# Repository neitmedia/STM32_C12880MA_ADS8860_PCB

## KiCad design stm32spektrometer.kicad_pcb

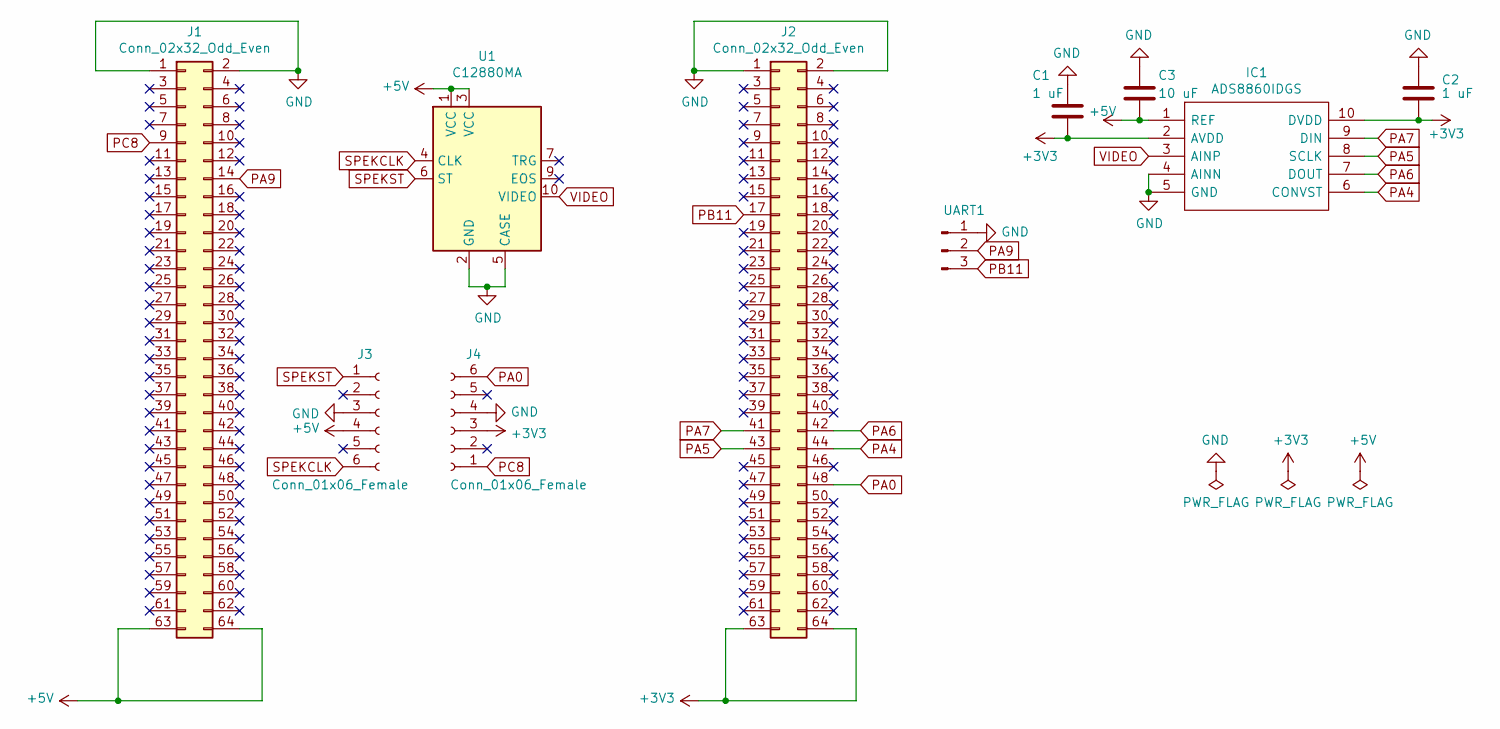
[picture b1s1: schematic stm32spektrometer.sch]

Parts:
C1, C2: 1 uF; C_0805_2012Metric
C3: 10 uF; C_0805_2012Metric
IC1: ADS8860IDGS; SOP50P490X110-10N; Mouser Part Number 595-ADS8860IDGS
J1, J2: Conn_02x32_Odd_Even; PinSocket_2x32_P2.54mm_Vertical
J3, J4: Conn_01x06_Female; PinSocket_1x06_P2.54mm_Vertical
U1: C12880MA; Hamamatsu_C12880
UART1: PinHeader_1x03_P2.54mm_Vertical

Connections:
+3V3: C1.2, C2.2, IC1.2 (AVDD), IC1.10 (DVDD), J2.63, J2.64, J4.3
+5V: C3.2, IC1.1 (REF), J1.63, J1.64, J3.4, U1.1 (VCC), U1.3 (VCC)
GND: C1.1, C2.1, C3.1, IC1.4 (AINN), IC1.5 (GND), J1.1, J1.2, J2.1, J2.2, J3.3, J4.4, U1.2 (GND), U1.5 (CASE), UART1.1
PA0: J2.48, J4.6
PA4: IC1.6 (CONVST), J2.44
PA5: IC1.8 (SCLK), J2.43
PA6: IC1.7 (DOUT), J2.42
PA7: IC1.9 (DIN), J2.41
PA9: J1.14, UART1.2
PB11: J2.17, UART1.3
PC8: J1.9, J4.1
SPEKCLK: J3.6, U1.4 (CLK)
SPEKST: J3.1, U1.6 (ST)
VIDEO: IC1.3 (AINP), U1.10 (VIDEO)

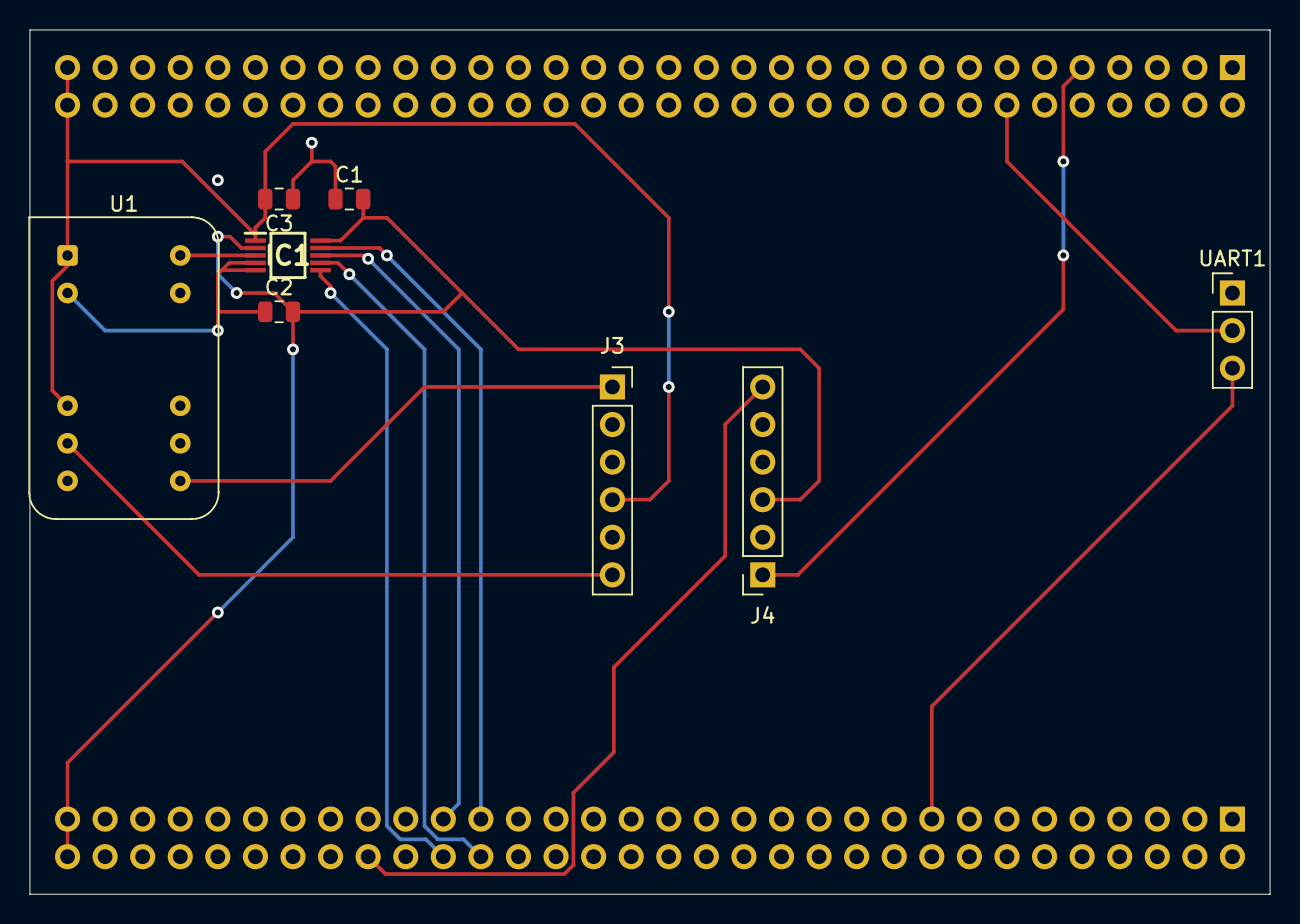
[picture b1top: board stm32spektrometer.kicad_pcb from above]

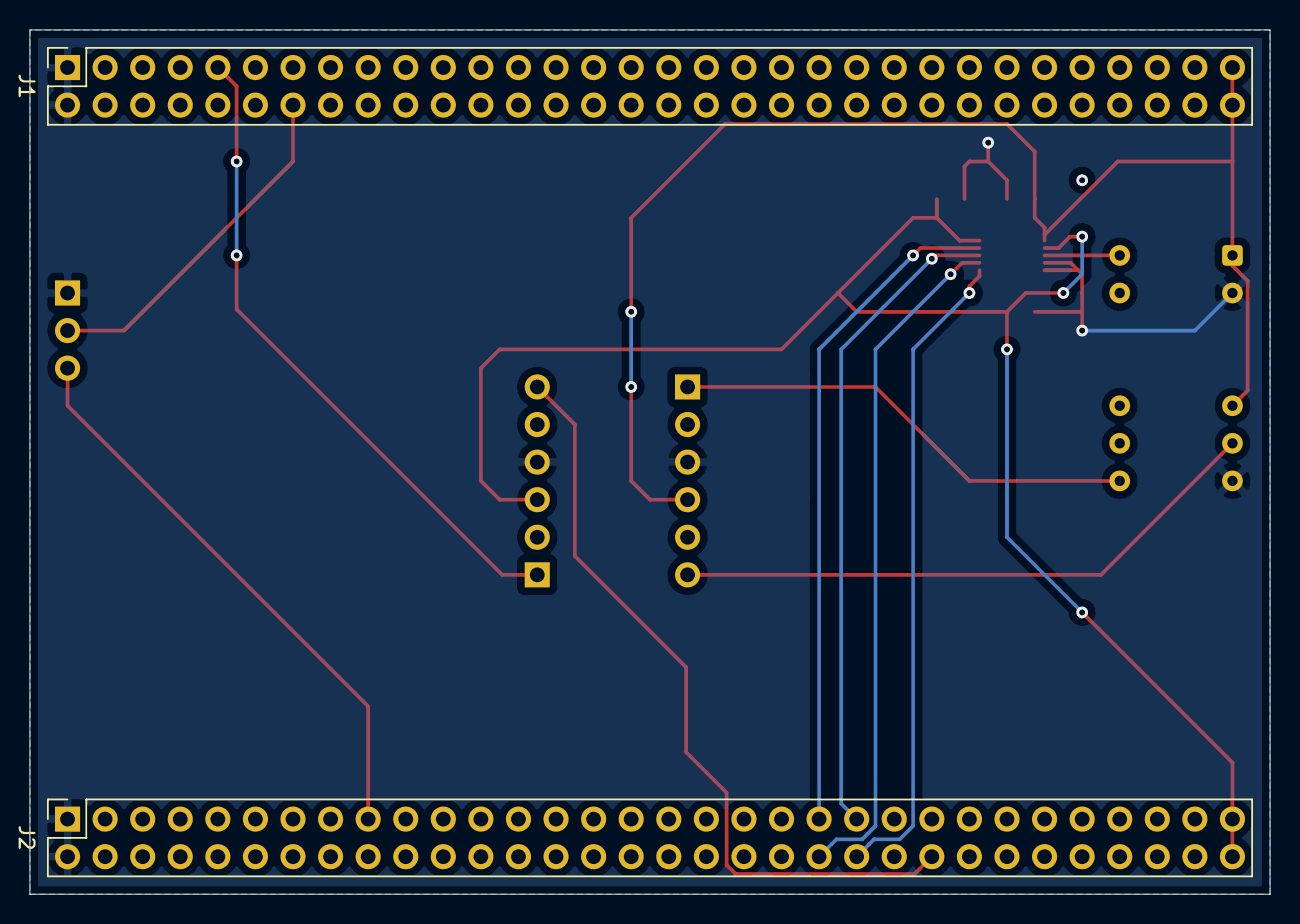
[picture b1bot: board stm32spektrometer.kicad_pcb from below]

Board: 2 copper layers, 83.8 x 58.4 mm, 10 parts (2 on the bottom side), 14 nets.
